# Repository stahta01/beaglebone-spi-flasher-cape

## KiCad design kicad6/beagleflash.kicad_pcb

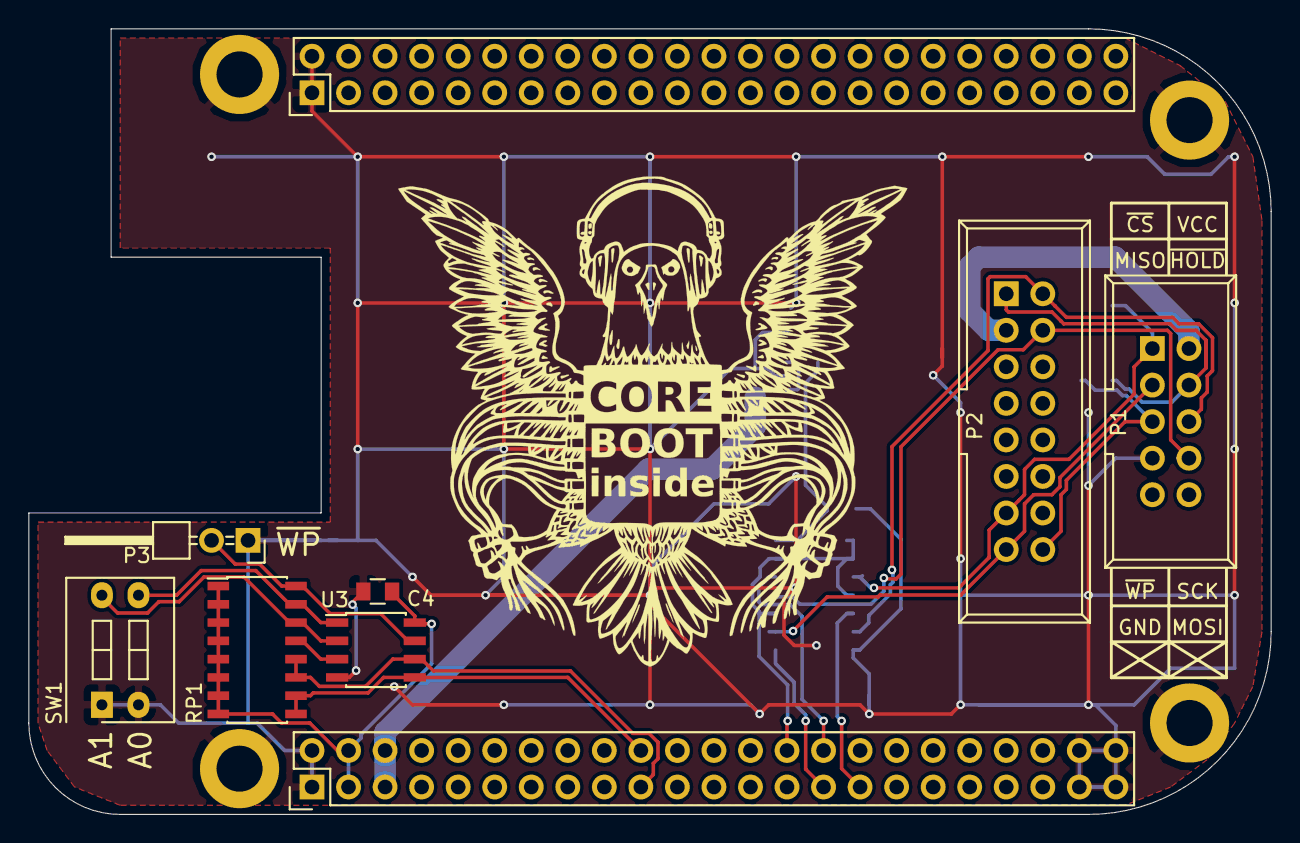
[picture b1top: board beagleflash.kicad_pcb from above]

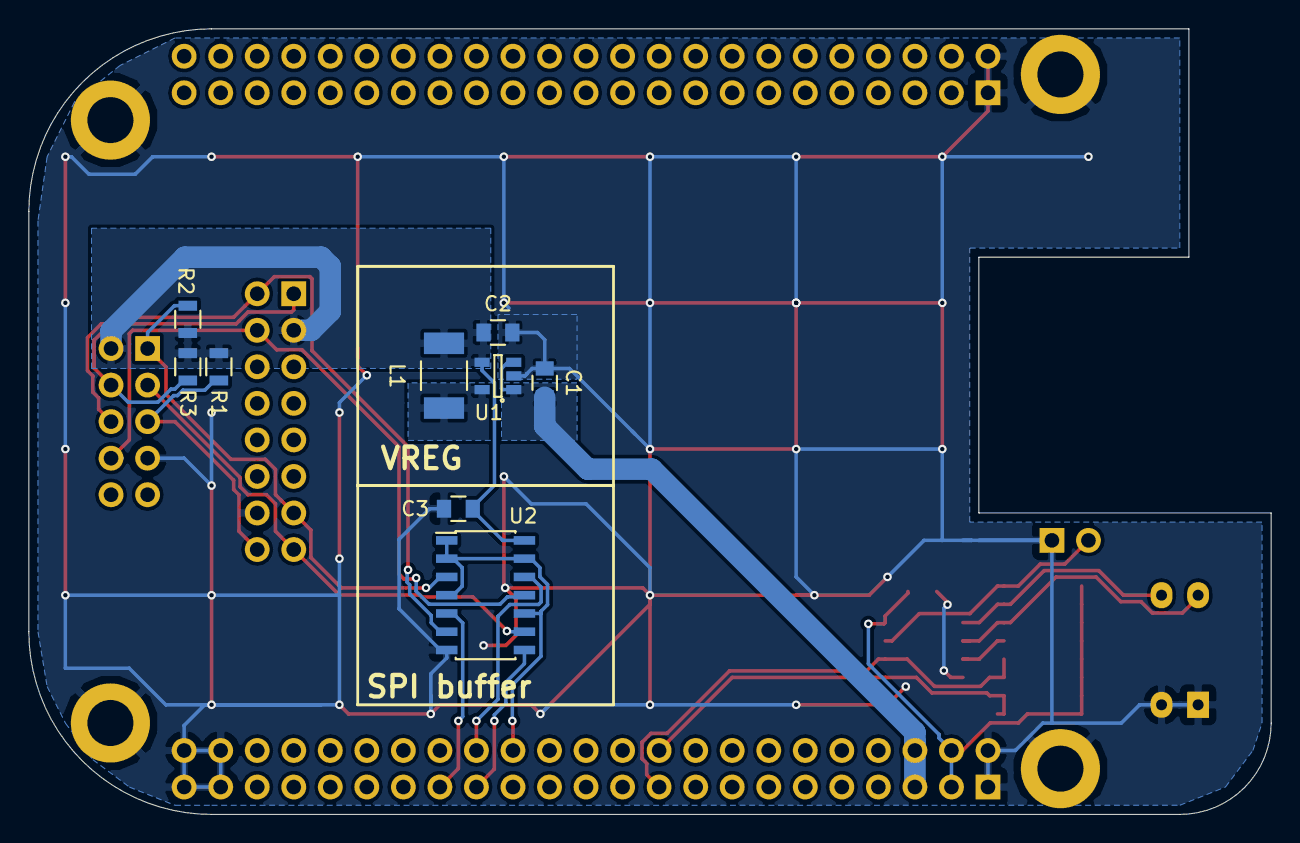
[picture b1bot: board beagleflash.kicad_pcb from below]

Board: 2 copper layers, 86.4 x 54.6 mm, 22 parts (9 on the bottom side), 21 nets.

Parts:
C1, C2, C3: 10uF; C_0805
C4: 0.1uF; C_0805
L1: 10uH; Neosid_Inductor_SM-NE45_SMD1812
P1: SPI-8; IDC_Header_Straight_10pins
P2: SPI-16; IDC_Header_Straight_16pins
P3: EEPROM_PROG_EN; Pin_Header_Angled_2x01
P4: BBB_P9; Pin_Header_Straight_2x23
P5: BBB_P8; Pin_Header_Straight_2x23
P6, P7, P8, P9: CONN_01X01; MountingHole_3.2mm_M3_ISO14580_Pad
R1, R2, R3: 10k; R_0805
RP1: 10k; SOIC-16_3.9x9.9mm_Pitch1.27mm
SW1: DIPS_02; SW_DIP_x2_Slide
U1: PAM2305AAB330; SOT-23-5
U2: 74HC125; SOIC-14_3.9x8.7mm_Pitch1.27mm
U3: CAT24C256W; SOIC-8_3.9x4.9mm_Pitch1.27mm

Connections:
+3V3: C4.1, P4.3, P4.4, RP1.1, RP1.2, RP1.3, RP1.4, RP1.5, RP1.6, RP1.7, RP1.8, U3.8
+5V: C1.1, P4.5, P4.6, U1.1, U1.3
/A0: RP1.15, SW1.3, U3.1
/A1: RP1.14, SW1.4, U3.2
/A2: RP1.13, U3.3
/CONN_MISO: P1.3, P2.15, U2.9
/CONN_MOSI: P1.8, P2.4, U2.11
/CONN_SCK: P1.6, P2.2, U2.6
/I2C2_SCL: P4.19, RP1.11, RP1.12, U3.6
/I2C2_SDA: P4.20, RP1.9, RP1.10, U3.5
/SPI_D0: P4.29, U2.8
/SPI_D1: P4.30, U2.12
/SPI_SCLK: P4.31, U2.5
/~CONN_CS: P1.1, P2.13, R2.2, U2.3
/~CONN_HOLD: P1.4, P2.1, R3.2
/~CONN_WP: P1.5, P2.16, R1.2
/~SPI_CS0: P4.28, U2.1, U2.2, U2.4, U2.10, U2.13
/~WP: P3.2, RP1.16, U3.7
GND: C1.2, C2.2, C3.2, C4.2, P1.7, P2.14, P3.1, P4.1, P4.2, P4.43, P4.44, P4.45, P4.46, P5.1, P5.2, P6.1, P7.1, P8.1, P9.1, SW1.1, SW1.2, U1.2, U2.7, U3.4
unnamed: L1.1, U1.5
VCC: C2.1, C3.1, L1.2, P1.2, P2.3, R1.1, R2.1, R3.1, U1.4, U2.14

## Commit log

2022-04-30 kicad6: Add kicad 5 files to folder kicad6
2022-04-30 kicad6: Update to kicad version 6
2022-04-30 kicad6: Fix most of the ERC warnings
